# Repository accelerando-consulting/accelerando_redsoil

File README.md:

# Accelerando Redsoil

This is a simple breakout board for the eByte E73 module with nrf52840
microcontroller.  This board requires minimal parts, in fact it can
work with only the module and no other parts.

There is a space for a LED on the front (pin 1.04) and it is possible
to add buttons on the back by soldering to an IO pin and the ground plane.

The board can be used with Arduino (Sandeep Mistry's nrf port with the
generic nrf52 target), or Zephyr OS using the included board
definition.

There is also a board definition for the Adafruit nrf52 bootloader,
and for CircuitPython, which make the board a fully compliant
CircuitPython target.

The circuit board files (for KiCad 5) are included.

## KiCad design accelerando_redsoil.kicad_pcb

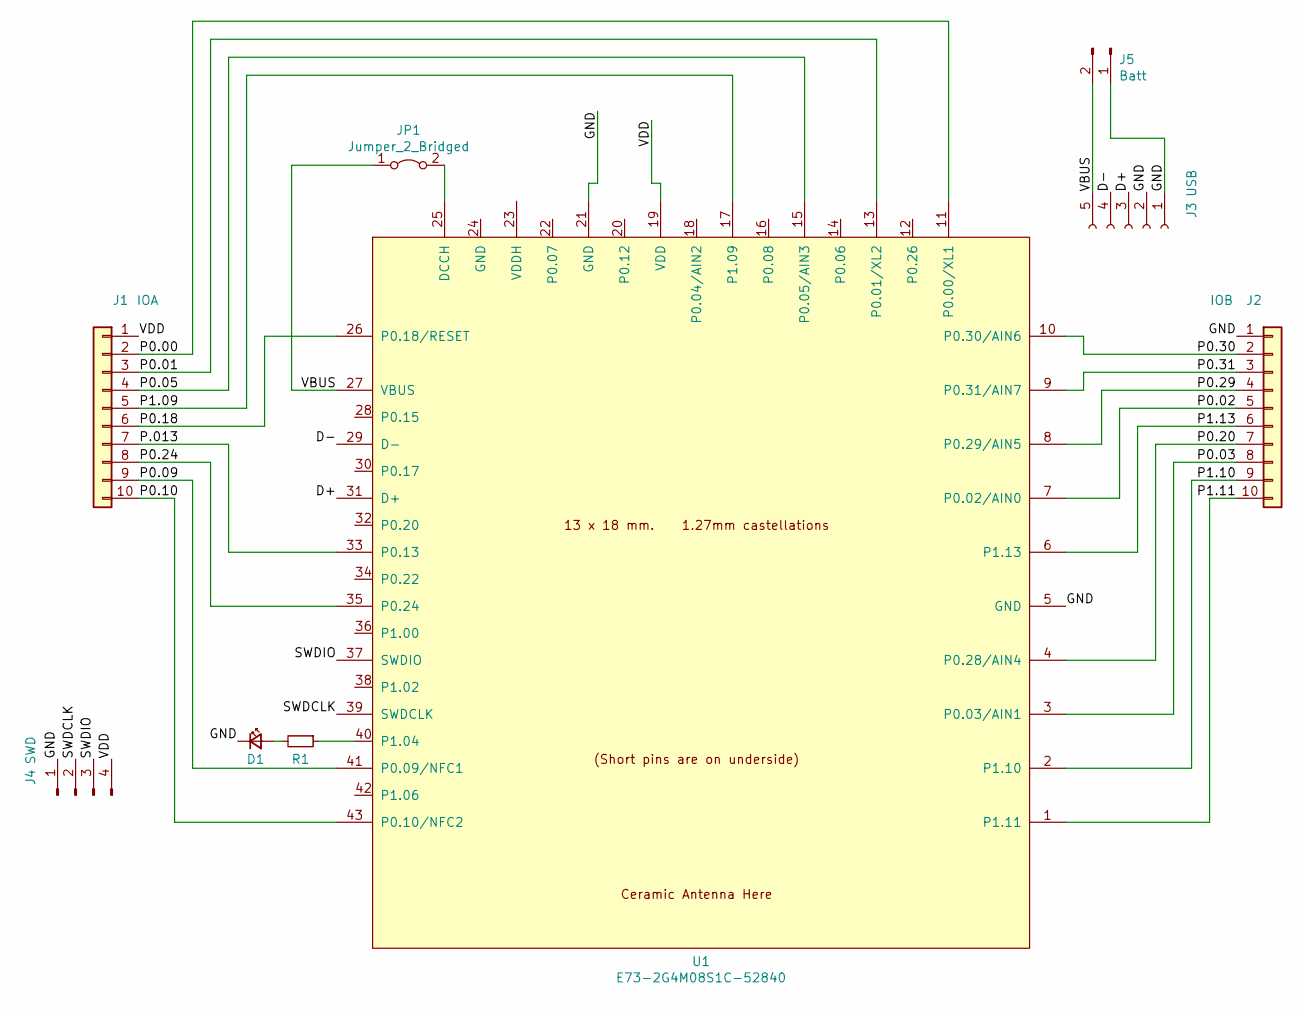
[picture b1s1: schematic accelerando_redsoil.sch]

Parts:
D1: LED_Small; LED_0603_1608Metric
J1: IOA; PinHeader_1x10_P2.54mm_Vertical
J2: IOB; PinHeader_1x10_P2.54mm_Vertical
J3: USB; PinHeader_1x05_P2.54mm_Vertical
J4: SWD; JST_PH_S4B-PH-K_1x04_P2.00mm_Horizontal
J5: Batt; PinHeader_1x02_P1.27mm_Vertical
JP1: Jumper_2_Bridged; SolderJumper-2_P1.3mm_Open_RoundedPad1.0x1.5mm
R1: R_Small; R_0603_1608Metric
U1: E73-2G4M08S1C-52840

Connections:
/D+: J3.3, U1.31 (D+)
/D-: J3.4, U1.29 (D-)
/GND: D1.1 (K), J2.1, J3.1, J3.2, J4.1, J5.1, U1.5 (GND), U1.21 (GND)
/P0.00: J1.2, U1.11 (P0.00/XL1)
/P0.01: J1.3, U1.13 (P0.01/XL2)
/P0.02: J2.5, U1.7 (P0.02/AIN0)
/P0.03: J2.8, U1.3 (P0.03/AIN1)
/P0.05: J1.4, U1.15 (P0.05/AIN3)
/P0.09: J1.9, U1.41 (P0.09/NFC1)
/P0.10: J1.10, U1.43 (P0.10/NFC2)
/P0.18: J1.6, U1.26 (P0.18/RESET)
/P0.20: J2.7, U1.4 (P0.28/AIN4)
/P0.24: J1.8, U1.35 (P0.24)
/P0.29: J2.4, U1.8 (P0.29/AIN5)
/P0.30: J2.2, U1.10 (P0.30/AIN6)
/P0.31: J2.3, U1.9 (P0.31/AIN7)
/P1.09: J1.5, U1.17 (P1.09)
/P1.10: J2.9, U1.2 (P1.10)
/P1.11: J2.10, U1.1 (P1.11)
/P1.13: J2.6, U1.6 (P1.13)
/P.013: J1.7, U1.33 (P0.13)
/SWDCLK: J4.2, U1.39 (SWDCLK)
/SWDIO: J4.3, U1.37 (SWDIO)
/VBUS: J3.5, J5.2, JP1.1 (A), U1.27 (VBUS)
/VDD: J1.1, J4.4, U1.19 (VDD)
unnamed: D1.2 (A), R1.2
unnamed: JP1.2 (B), U1.25 (DCCH)
unnamed: R1.1, U1.40 (P1.04)

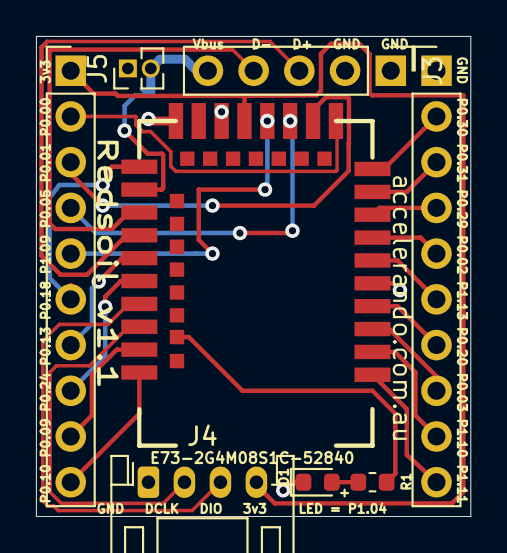
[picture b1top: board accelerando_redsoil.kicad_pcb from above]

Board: 2 copper layers, 24.1 x 26.7 mm, 9 parts (1 on the bottom side), 28 nets.

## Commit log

2021-04-19 Accelerando Redsoil - Open Source nrf52840 breakout board
2021-04-19 Board definition for Adafruit bootloader
2021-04-19 Board definition for Circuit Python
2021-04-19 Board definition for Zephyr
2021-04-19 Add README and LICENSE
2021-04-20 Redsoil PCB 1.1 - USB power, Battery conn, JST PH SWD
2021-04-22 Use underscore not hyphen in zephyr board name
2021-04-22 Fix the pin number of pin 1.11 in circuitpython
2021-04-27 s/BSD/MIT/
2021-04-27 Use USB id 1209:ACC1 as allocated by pidcodes.github.com (thanks pidcodes!)

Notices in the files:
accelerando_redsoil.kicad_pcb:
©2020 accelerando.com.au
